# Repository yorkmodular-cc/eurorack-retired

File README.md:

# eurorack-retired

This repo contains schematics, panel files and suchlike for my 'retired' and/or discontinued Eurorack modules. 

They are placed here in the hope that they may be useful to some people - in a lot of the cases I've either refined the design or shelved it altogether. No warranty is given or implied - all of the designs are known to work but I accept no responsibility if you screw something up.

This info is free and unencumbered and released into the public domain.

In jurisdictions that recognize copyright laws, the author or authors
of this software dedicate any and all copyright interest in the
software to the public domain. We make this dedication for the benefit
of the public at large and to the detriment of our heirs and
successors. We intend this dedication to be an overt act of
relinquishment in perpetuity of all present and future rights to this
information e under copyright law.

THESE DESIGNS ARE PROVIDED "AS IS", WITHOUT WARRANTY OF ANY KIND,
EXPRESS OR IMPLIED, INCLUDING BUT NOT LIMITED TO THE WARRANTIES OF
MERCHANTABILITY, FITNESS FOR A PARTICULAR PURPOSE AND NONINFRINGEMENT.
IN NO EVENT SHALL THE AUTHORS BE LIABLE FOR ANY CLAIM, DAMAGES OR
OTHER LIABILITY, WHETHER IN AN ACTION OF CONTRACT, TORT OR OTHERWISE,
ARISING FROM, OUT OF OR IN CONNECTION WITH THE SOFTWARE OR THE USE OR
OTHER DEALINGS IN THE SOFTWARE.

For more information, please refer to <http://unlicense.org/>

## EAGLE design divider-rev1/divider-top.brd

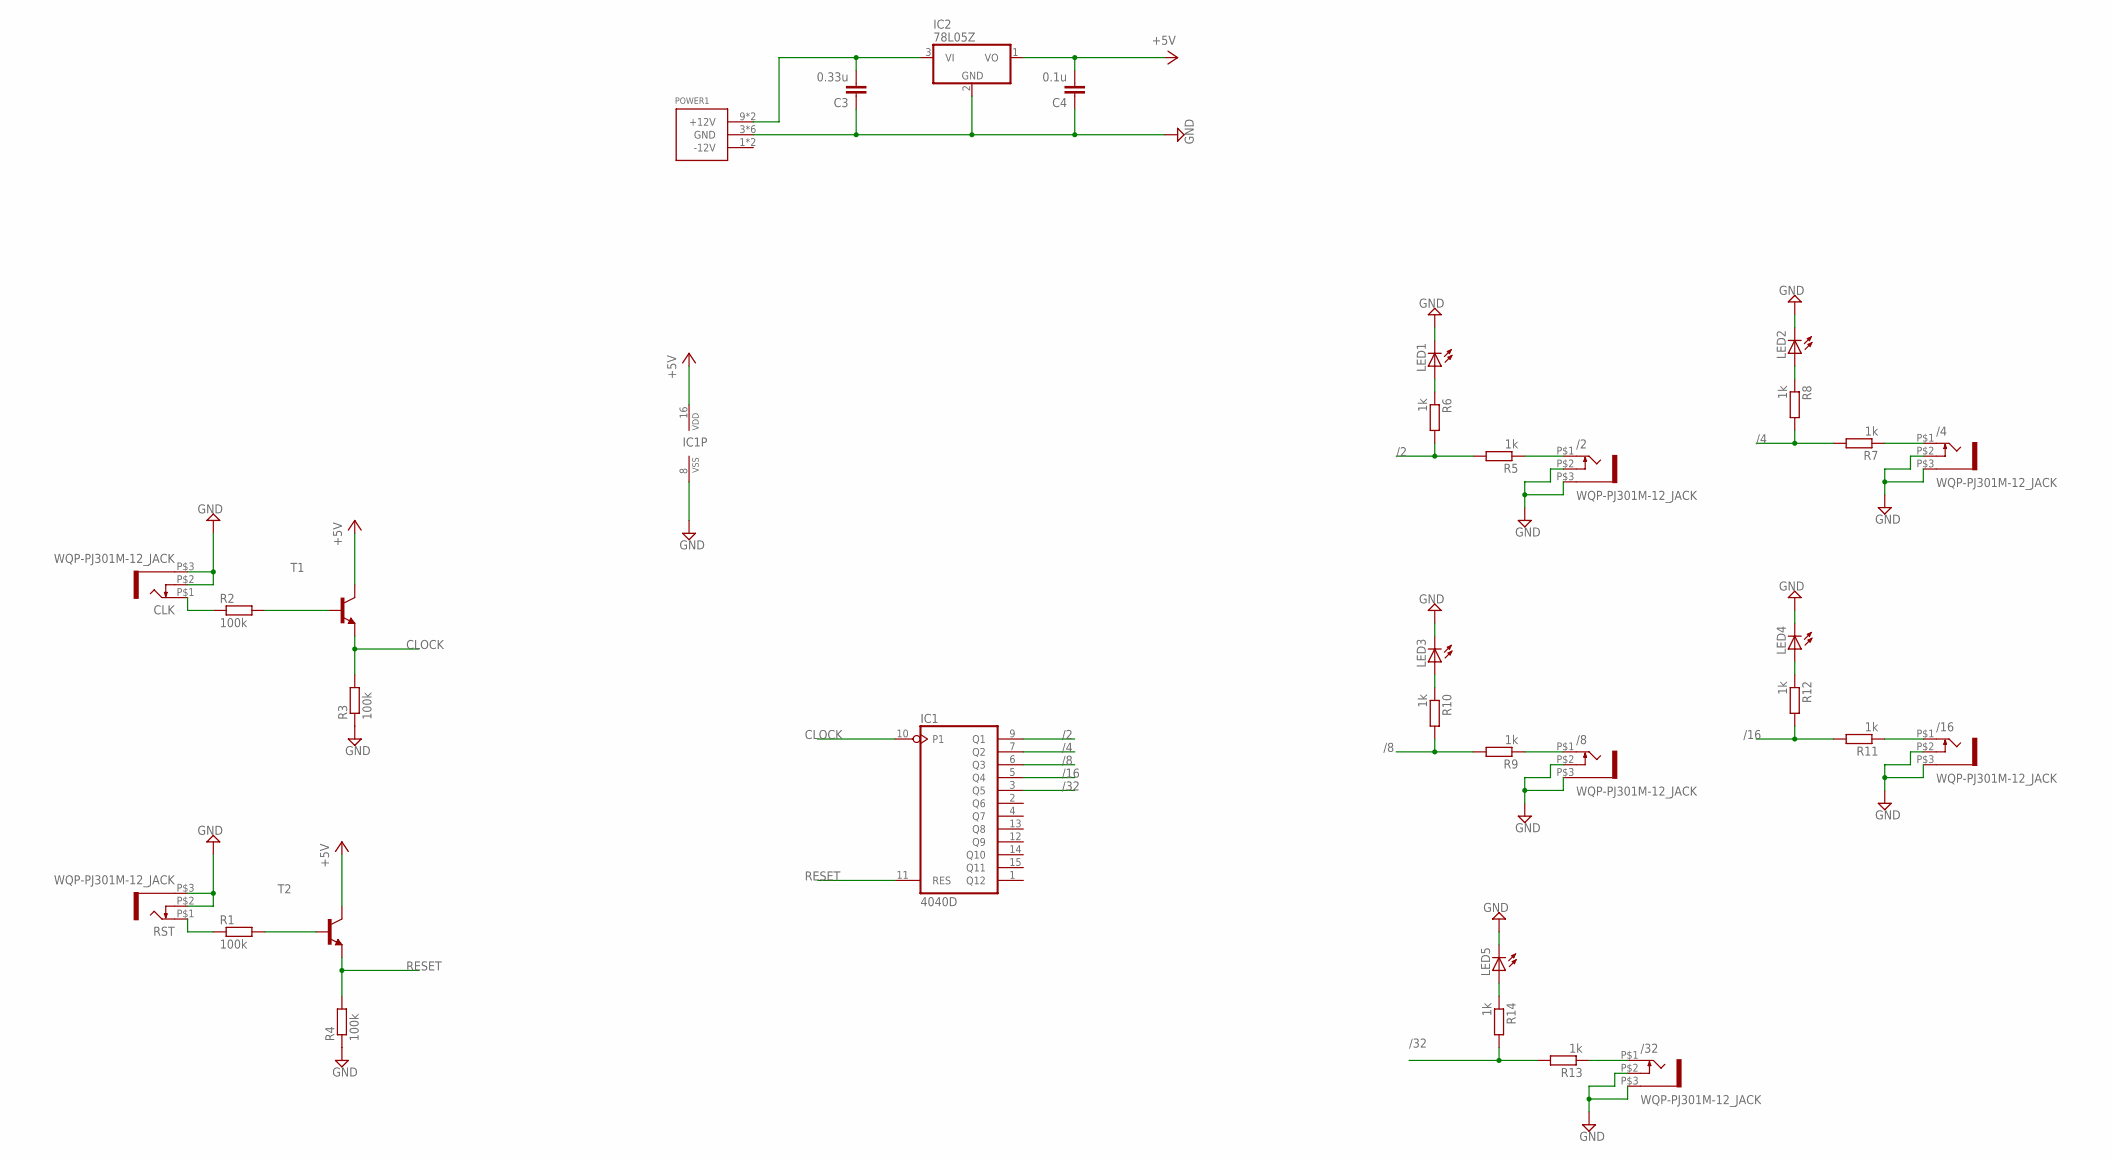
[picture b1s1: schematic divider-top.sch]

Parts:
/2, /4, /8, /16, /32: WQP-PJ301M-12_JACK
C3: 0.33u; C0805
C4: 0.1u; C0805
CLK: WQP-PJ301M-12_JACK
IC1: 4040D; SO16
IC2: 78L05Z; TO92
LED1, LED2, LED3, LED4, LED5: LEDCHIP-LED0805; CHIP-LED0805
POWER1: POWER_SIMPLE10; POWER_10
R1, R2, R3, R4: 100k; R0805
R5, R6, R7, R8, R9, R10, R11, R12, R13, R14: 1k; R0805
RST: WQP-PJ301M-12_JACK
T1, T2: MMBT3904LT1-NPN-SOT23-BEC; SOT23-BEC

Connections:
+5V: C4.2, IC1.16 (VDD), IC2.1 (VO), T1.C, T2.C
/2: IC1.9 (Q1), R5.2, R6.2
/4: IC1.7 (Q2), R7.2, R8.2
/8: IC1.6 (Q3), R9.2, R10.2
/16: IC1.5 (Q4), R11.2, R12.2
/32: IC1.3 (Q5), R13.2, R14.2
CLOCK: IC1.10 (P1), R3.2, T1.E
GND: /2.P$2 (3), /2.P$3 (1), /4.P$2 (3), /4.P$3 (1), /8.P$2 (3), /8.P$3 (1), /16.P$2 (3), /16.P$3 (1), /32.P$2 (3), /32.P$3 (1), C3.1, C4.1, CLK.P$2 (3), CLK.P$3 (1), IC1.8 (VSS), IC2.2 (GND), LED1.C, LED2.C, LED3.C, LED4.C, LED5.C, POWER1.3 (GND), POWER1.4 (GND), POWER1.5 (GND), POWER1.6 (GND), POWER1.7 (GND), POWER1.8 (GND), R3.1, R4.1, RST.P$2 (3), RST.P$3 (1)
unnamed: R1.1, RST.P$1 (2)
unnamed: R1.2, T2.B
unnamed: CLK.P$1 (2), R2.1
unnamed: /2.P$1 (2), R5.1
unnamed: R2.2, T1.B
unnamed: /32.P$1 (2), R13.1
unnamed: LED1.A, R6.1
unnamed: LED5.A, R14.1
unnamed: /4.P$1 (2), R7.1
unnamed: LED2.A, R8.1
unnamed: /8.P$1 (2), R9.1
unnamed: LED3.A, R10.1
unnamed: /16.P$1 (2), R11.1
unnamed: LED4.A, R12.1
unnamed: C3.2, IC2.3 (VI), POWER1.9 (+12V), POWER1.10 (+12V)
RESET: IC1.11 (RES), R4.2, T2.E

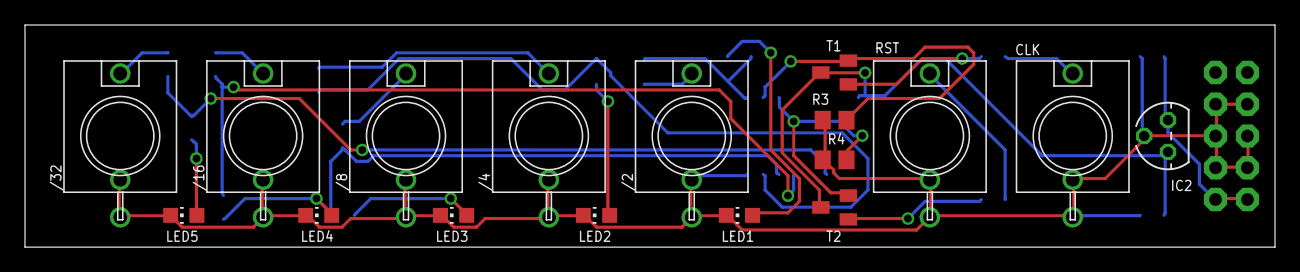
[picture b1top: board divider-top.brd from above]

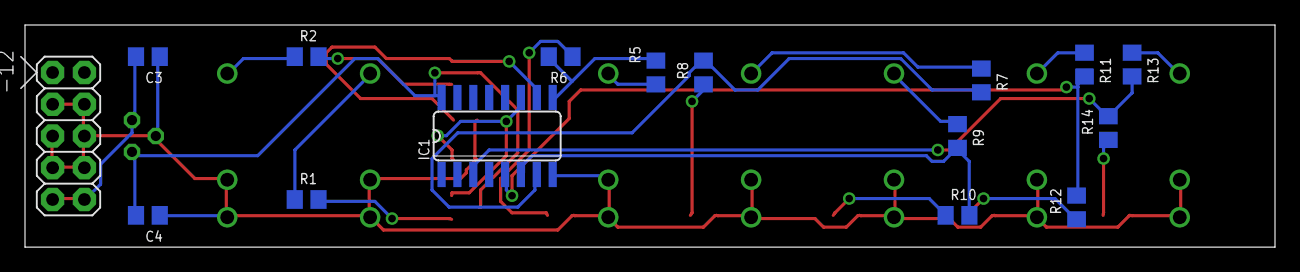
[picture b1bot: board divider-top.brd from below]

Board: 2 copper layers, 100.0 x 17.8 mm, 33 parts (16 on the bottom side), 24 nets.

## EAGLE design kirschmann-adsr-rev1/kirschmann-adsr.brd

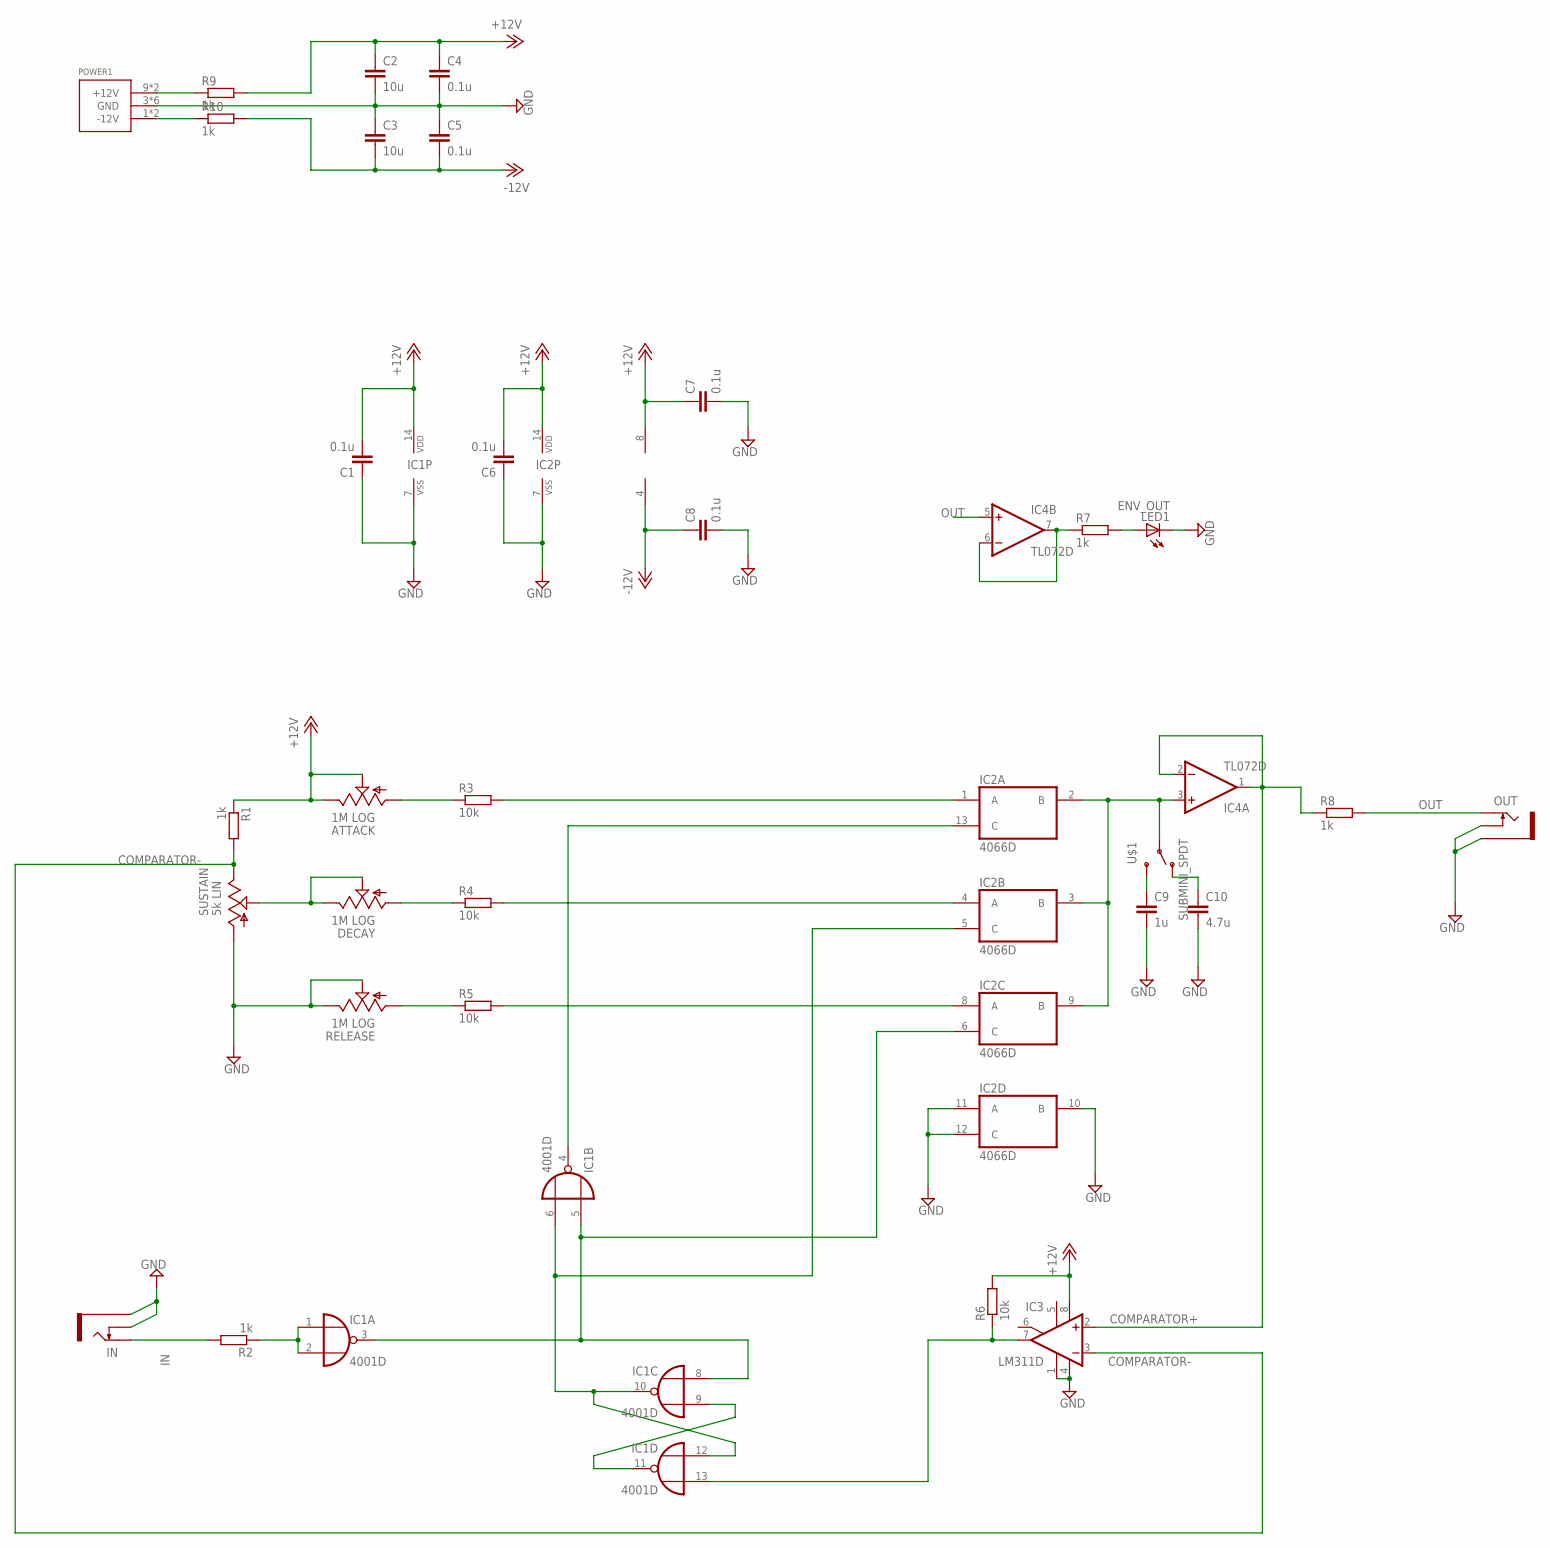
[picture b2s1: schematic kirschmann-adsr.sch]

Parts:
ATTACK: 1M LOG; 9MM_SNAP-IN_POT
C1, C4, C5, C6, C7, C8: 0.1u; C0805
C2, C3: 10u; C0805
C9: 1u; C0805
C10: 4.7u; C0805
DECAY: 1M LOG; 9MM_SNAP-IN_POT
IC1: 4001D; SO14
IC2: 4066D; SO14
IC3: LM311D; SO08
IC4: TL072D; SO08
IN: THONKICONNNEW; WQP-PJ301M-12_JACK
LED1: ENV_OUT; LED3MM
OUT: THONKICONNNEW; WQP-PJ301M-12_JACK
POWER1: POWER_SIMPLE10; POWER_10
R1, R2, R7, R8, R9, R10: 1k; R0805
R3, R4, R5, R6: 10k; R0805
RELEASE: 1M LOG; 9MM_SNAP-IN_POT
SUSTAIN: 5k LIN; 9MM_SNAP-IN_POT
U$1: SUBMINI_SPDT; SUBMINI_TOGGLE

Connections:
+12V: ATTACK.2 (S), ATTACK.3 (E), C1.2, C2.1, C4.1, C6.2, C7.1, IC1.14 (VDD), IC2.14 (VDD), IC3.8 (V+), IC4.8 (V+), R1.1, R6.2, R9.2
-12V: C3.2, C5.2, C8.1, IC4.4 (V-), R10.2
COMPARATOR+: IC3.2 (+IN), IC4.1 (OUT), IC4.2 (-IN), R8.1
COMPARATOR-: IC3.3 (-IN), R1.2, SUSTAIN.3 (E)
GND: C1.1, C2.2, C3.1, C4.2, C5.1, C6.1, C7.2, C8.2, C9.2, C10.2, IC1.7 (VSS), IC2.7 (VSS), IC2.10 (B), IC2.11 (A), IC2.12 (C), IC3.1 (GND), IC3.4 (V-), IN.P$2_SWITCH (SWITCH), IN.P$3_SLEEVE (SLEEVE), LED1.K (C), OUT.P$2_SWITCH (SWITCH), OUT.P$3_SLEEVE (SLEEVE), POWER1.3 (GND), POWER1.4 (GND), POWER1.5 (GND), POWER1.6 (GND), POWER1.7 (GND), POWER1.8 (GND), RELEASE.2 (S), RELEASE.3 (E), SUSTAIN.1 (A)
IN: IN.P$1_TIP (TIP), R2.2
unnamed: IC1.6 (I1), IC1.10 (O), IC1.12 (I0), IC2.5 (C)
unnamed: IC1.9 (I1), IC1.11 (O)
unnamed: IC2.8 (A), R5.2
unnamed: C9.1, U$1.3 (S)
unnamed: IC1.13 (I1), IC3.7 (OUT), R6.1
unnamed: DECAY.1 (A), R4.1
unnamed: R5.1, RELEASE.1 (A)
unnamed: IC1.3 (O), IC1.5 (I0), IC1.8 (I0), IC2.6 (C)
unnamed: IC1.4 (O), IC2.13 (C)
unnamed: IC2.2 (B), IC2.3 (B), IC2.9 (B), IC4.3 (+IN), U$1.COM (COMMON)
unnamed: C10.1, U$1.1 (O)
unnamed: IC1.1 (I0), IC1.2 (I1), R2.1
unnamed: IC2.4 (A), R4.2
unnamed: IC2.1 (A), R3.2
unnamed: IC4.6 (-IN), IC4.7 (OUT), R7.1
unnamed: LED1.A, R7.2
unnamed: DECAY.2 (S), DECAY.3 (E), SUSTAIN.2 (S)
unnamed: POWER1.9 (+12V), POWER1.10 (+12V), R9.1
unnamed: ATTACK.1 (A), R3.1
unnamed: POWER1.1 (-12V), POWER1.2 (-12V), R10.1
OUT: IC4.5 (+IN), OUT.P$1_TIP (TIP), R8.2

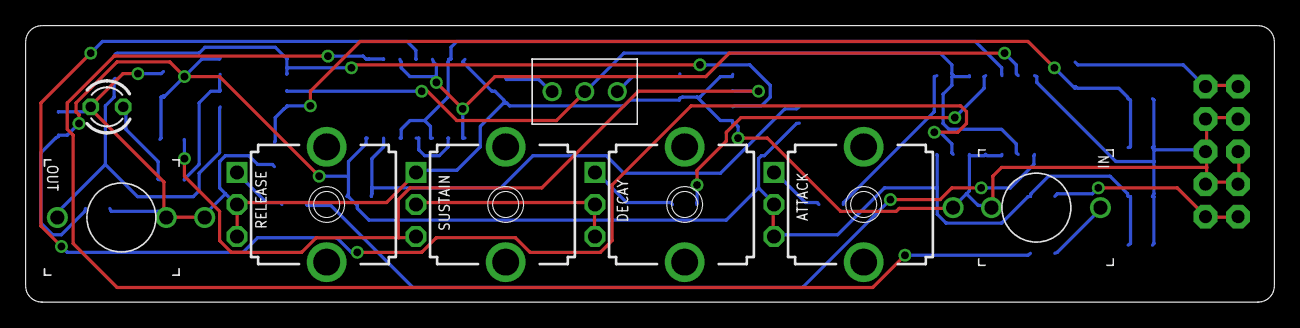
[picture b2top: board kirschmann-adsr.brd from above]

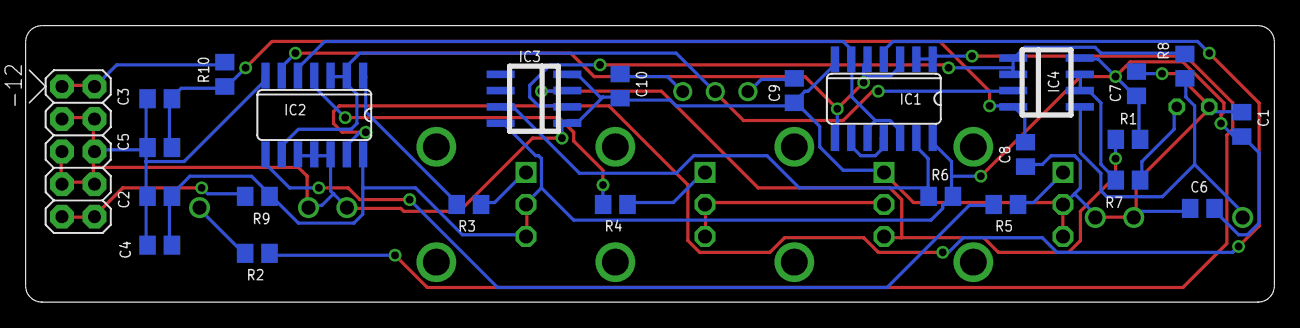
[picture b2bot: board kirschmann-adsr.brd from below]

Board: 2 copper layers, 97.5 x 21.6 mm, 33 parts (25 on the bottom side), 27 nets.

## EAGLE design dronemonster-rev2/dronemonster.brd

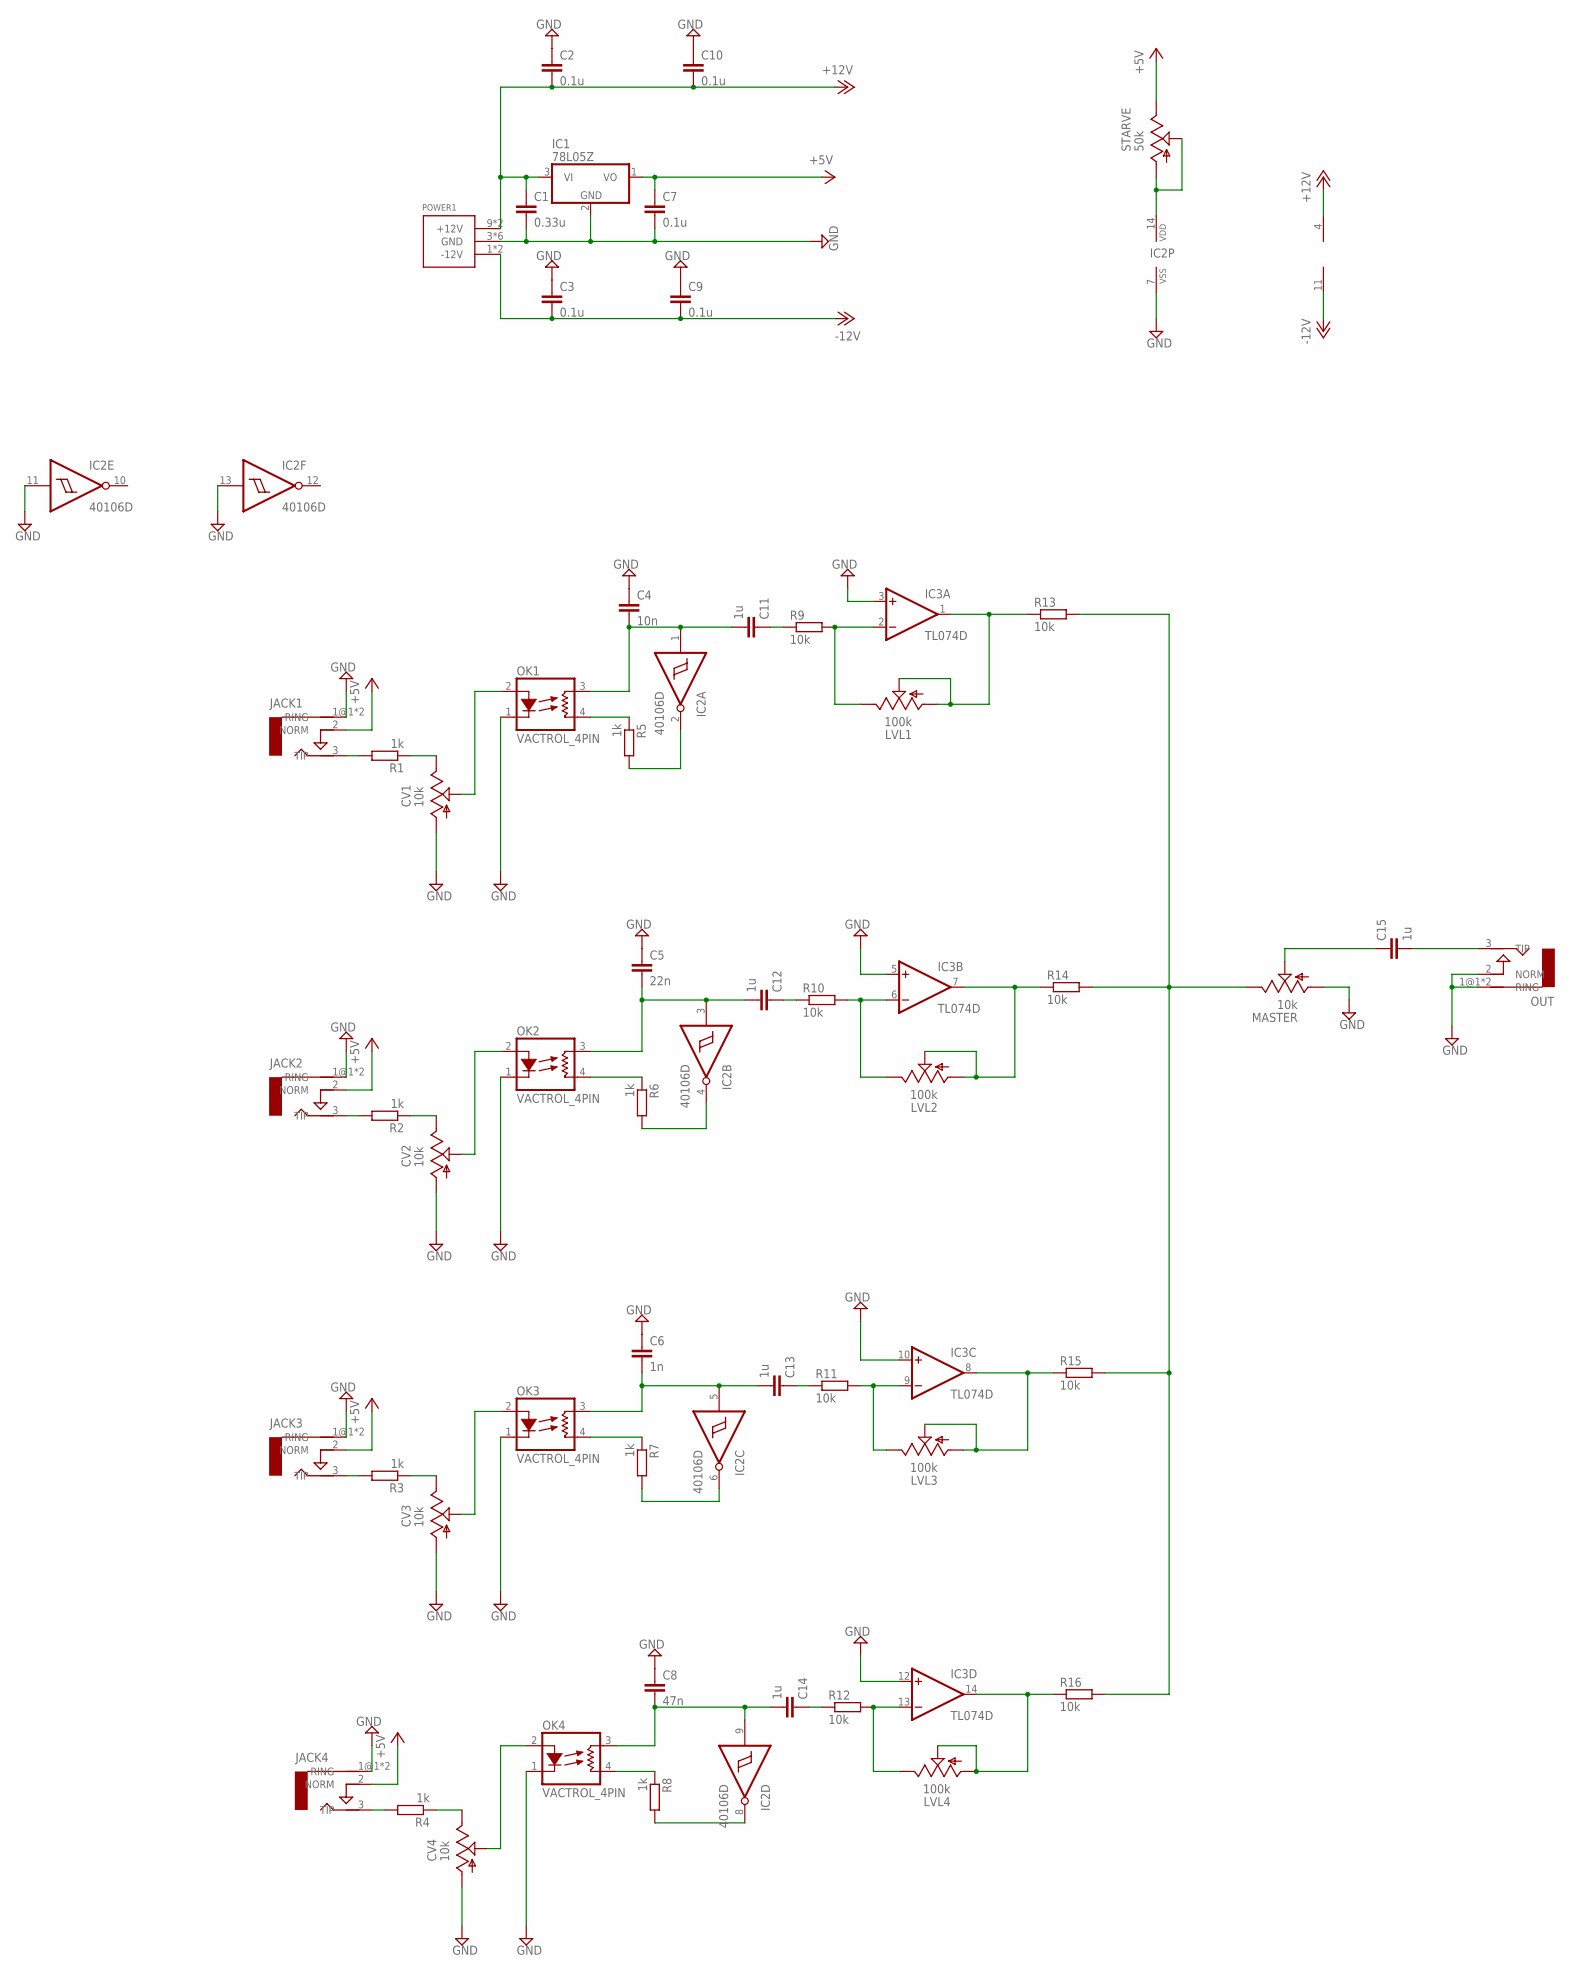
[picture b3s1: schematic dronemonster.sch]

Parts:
C1: 0.33u; C0805
C2, C3, C7, C9, C10: 0.1u; C0805
C4: 10n; C0805
C5: 22n; C0805
C6: 1n; C0805
C8: 47n; C0805
C11, C12, C13, C14, C15: 1u; C0805
CV1, CV2, CV3, CV4: 10k; 9MM_SNAP-IN_POT
IC1: 78L05Z; TO92
IC2: 40106D; SO14
IC3: TL074D; SO14
JACK1: IN1; ERTHENVAR-JACK
JACK2: IN2; ERTHENVAR-JACK
JACK3: IN3; ERTHENVAR-JACK
JACK4: IN4; ERTHENVAR-JACK
LVL1, LVL2, LVL3, LVL4: 100k; 9MM_SNAP-IN_POT
MASTER: 10k; 9MM_SNAP-IN_POT
OK1, OK2, OK3, OK4: VACTROL_4PIN; VACTROL_4PIN_VTL5C
OUT: OUT; ERTHENVAR-JACK
POWER1: POWER_SIMPLE10; POWER_10
R1, R2, R3, R4, R5, R6, R7, R8: 1k; R0805
R9, R10, R11, R12, R13, R14, R15, R16: 10k; R0805
STARVE: 50k; 9MM_SNAP-IN_POT

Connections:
+5V: C7.1, IC1.1 (VO), JACK1.2 (NORM), JACK2.2 (NORM), JACK3.2 (NORM), JACK4.2 (NORM), STARVE.3 (E)
+12V: C1.1, C2.2, C10.2, IC1.3 (VI), IC3.4 (V+), POWER1.9 (+12V), POWER1.10 (+12V)
-12V: C3.2, C9.2, IC3.11 (V-), POWER1.1 (-12V), POWER1.2 (-12V)
GND: C1.2, C2.1, C3.1, C4.1, C5.1, C6.1, C7.2, C8.1, C9.1, C10.1, CV1.1 (A), CV2.1 (A), CV3.1 (A), CV4.1 (A), IC1.2 (GND), IC2.7 (VSS), IC2.11 (I), IC2.13 (I), IC3.3 (+IN), IC3.5 (+IN), IC3.10 (+IN), IC3.12 (+IN), JACK1.1@1 (RING), JACK1.1@2 (RING), JACK2.1@1 (RING), JACK2.1@2 (RING), JACK3.1@1 (RING), JACK3.1@2 (RING), JACK4.1@1 (RING), JACK4.1@2 (RING), MASTER.1 (A), OK1.1 (LED-), OK2.1 (LED-), OK3.1 (LED-), OK4.1 (LED-), OUT.1@1 (RING), OUT.1@2 (RING), OUT.2 (NORM), POWER1.3 (GND), POWER1.4 (GND), POWER1.5 (GND), POWER1.6 (GND), POWER1.7 (GND), POWER1.8 (GND)
unnamed: C14.1, R12.1
unnamed: IC2.14 (VDD), STARVE.1 (A), STARVE.2 (S)
unnamed: JACK1.3 (TIP), R1.2
unnamed: CV1.2 (S), OK1.2 (LED+)
unnamed: C15.1, MASTER.2 (S)
unnamed: CV1.3 (E), R1.1
unnamed: C13.1, R11.1
unnamed: C12.1, R10.1
unnamed: C11.1, R9.1
unnamed: CV2.3 (E), R2.1
unnamed: IC3.13 (-IN), LVL4.3 (E), R12.2
unnamed: JACK2.3 (TIP), R2.2
unnamed: IC3.9 (-IN), LVL3.3 (E), R11.2
unnamed: CV2.2 (S), OK2.2 (LED+)
unnamed: IC3.6 (-IN), LVL2.3 (E), R10.2
unnamed: CV3.3 (E), R3.1
unnamed: IC3.2 (-IN), LVL1.3 (E), R9.2
unnamed: JACK3.3 (TIP), R3.2
unnamed: IC3.1 (OUT), LVL1.1 (A), LVL1.2 (S), R13.1
unnamed: CV3.2 (S), OK3.2 (LED+)
unnamed: MASTER.3 (E), R13.2, R14.2, R15.2, R16.2
unnamed: CV4.3 (E), R4.1
unnamed: C15.2, OUT.3 (TIP)
unnamed: JACK4.3 (TIP), R4.2
unnamed: CV4.2 (S), OK4.2 (LED+)
unnamed: IC3.14 (OUT), LVL4.1 (A), LVL4.2 (S), R16.1
unnamed: OK4.4 (RES2), R8.1
unnamed: IC2.8 (O), R8.2
unnamed: C8.2, C14.2, IC2.9 (I), OK4.3 (RES1)
unnamed: OK3.4 (RES2), R7.1
unnamed: IC2.6 (O), R7.2
unnamed: C6.2, C13.2, IC2.5 (I), OK3.3 (RES1)
unnamed: OK2.4 (RES2), R6.1
unnamed: IC2.4 (O), R6.2
unnamed: C5.2, C12.2, IC2.3 (I), OK2.3 (RES1)
unnamed: OK1.4 (RES2), R5.1
unnamed: IC2.2 (O), R5.2
unnamed: C4.2, C11.2, IC2.1 (I), OK1.3 (RES1)
unnamed: IC3.8 (OUT), LVL3.1 (A), LVL3.2 (S), R15.1
unnamed: IC3.7 (OUT), LVL2.1 (A), LVL2.2 (S), R14.1

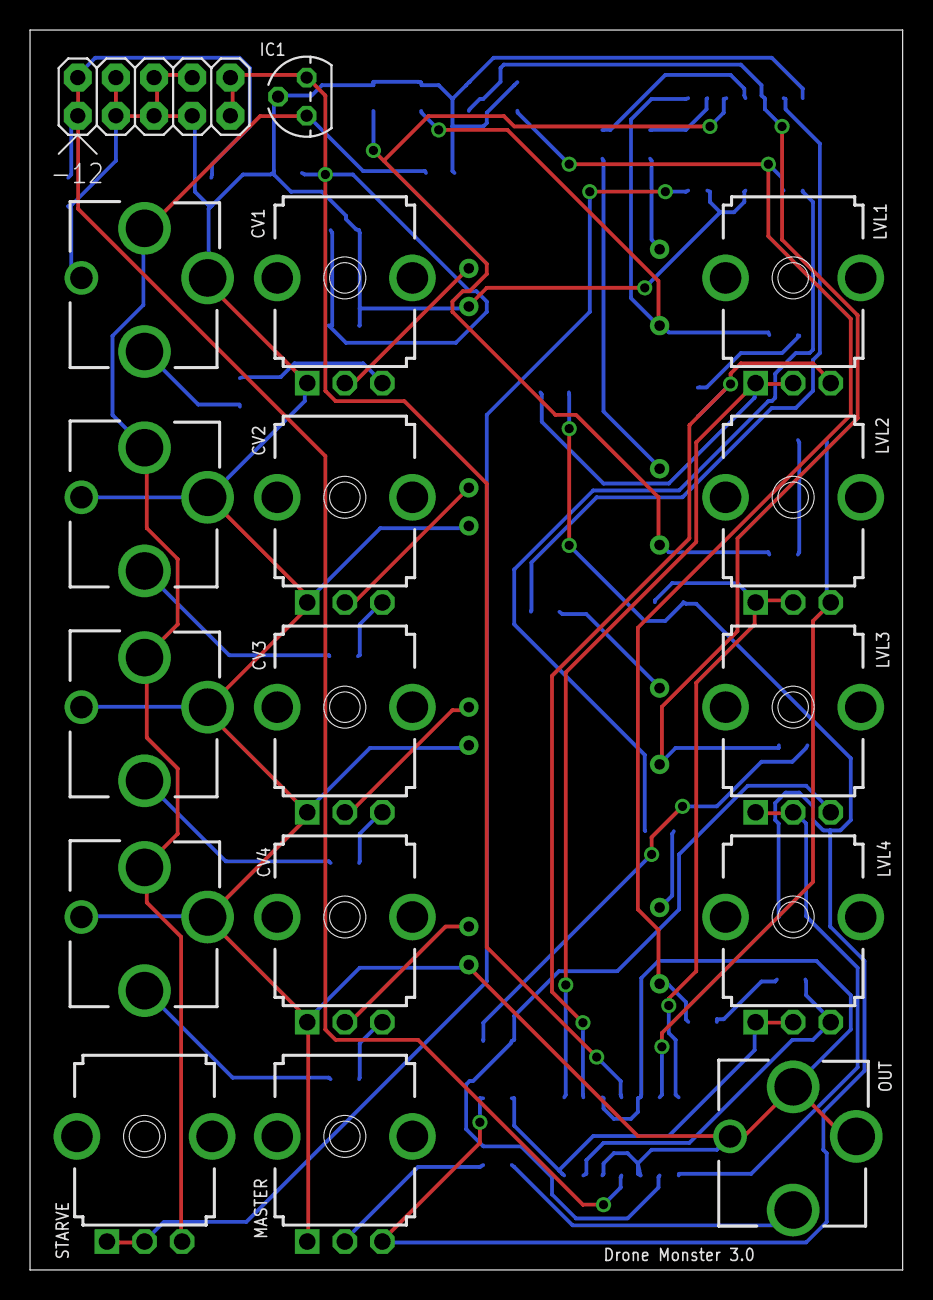
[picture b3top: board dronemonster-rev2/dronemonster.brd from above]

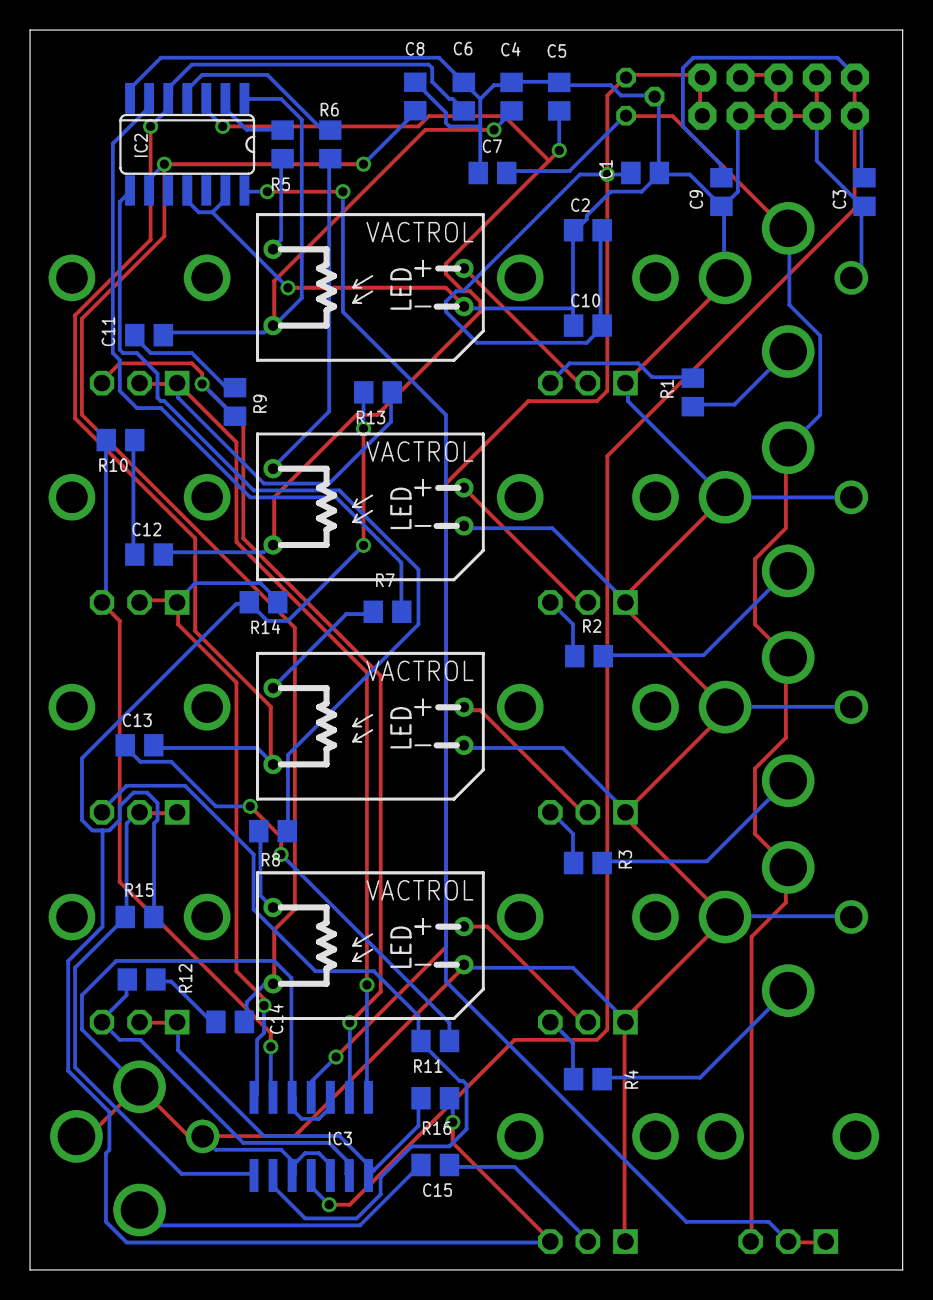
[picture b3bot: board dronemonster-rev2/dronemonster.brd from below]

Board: 2 copper layers, 58.1 x 82.5 mm, 54 parts (37 on the bottom side), 44 nets.

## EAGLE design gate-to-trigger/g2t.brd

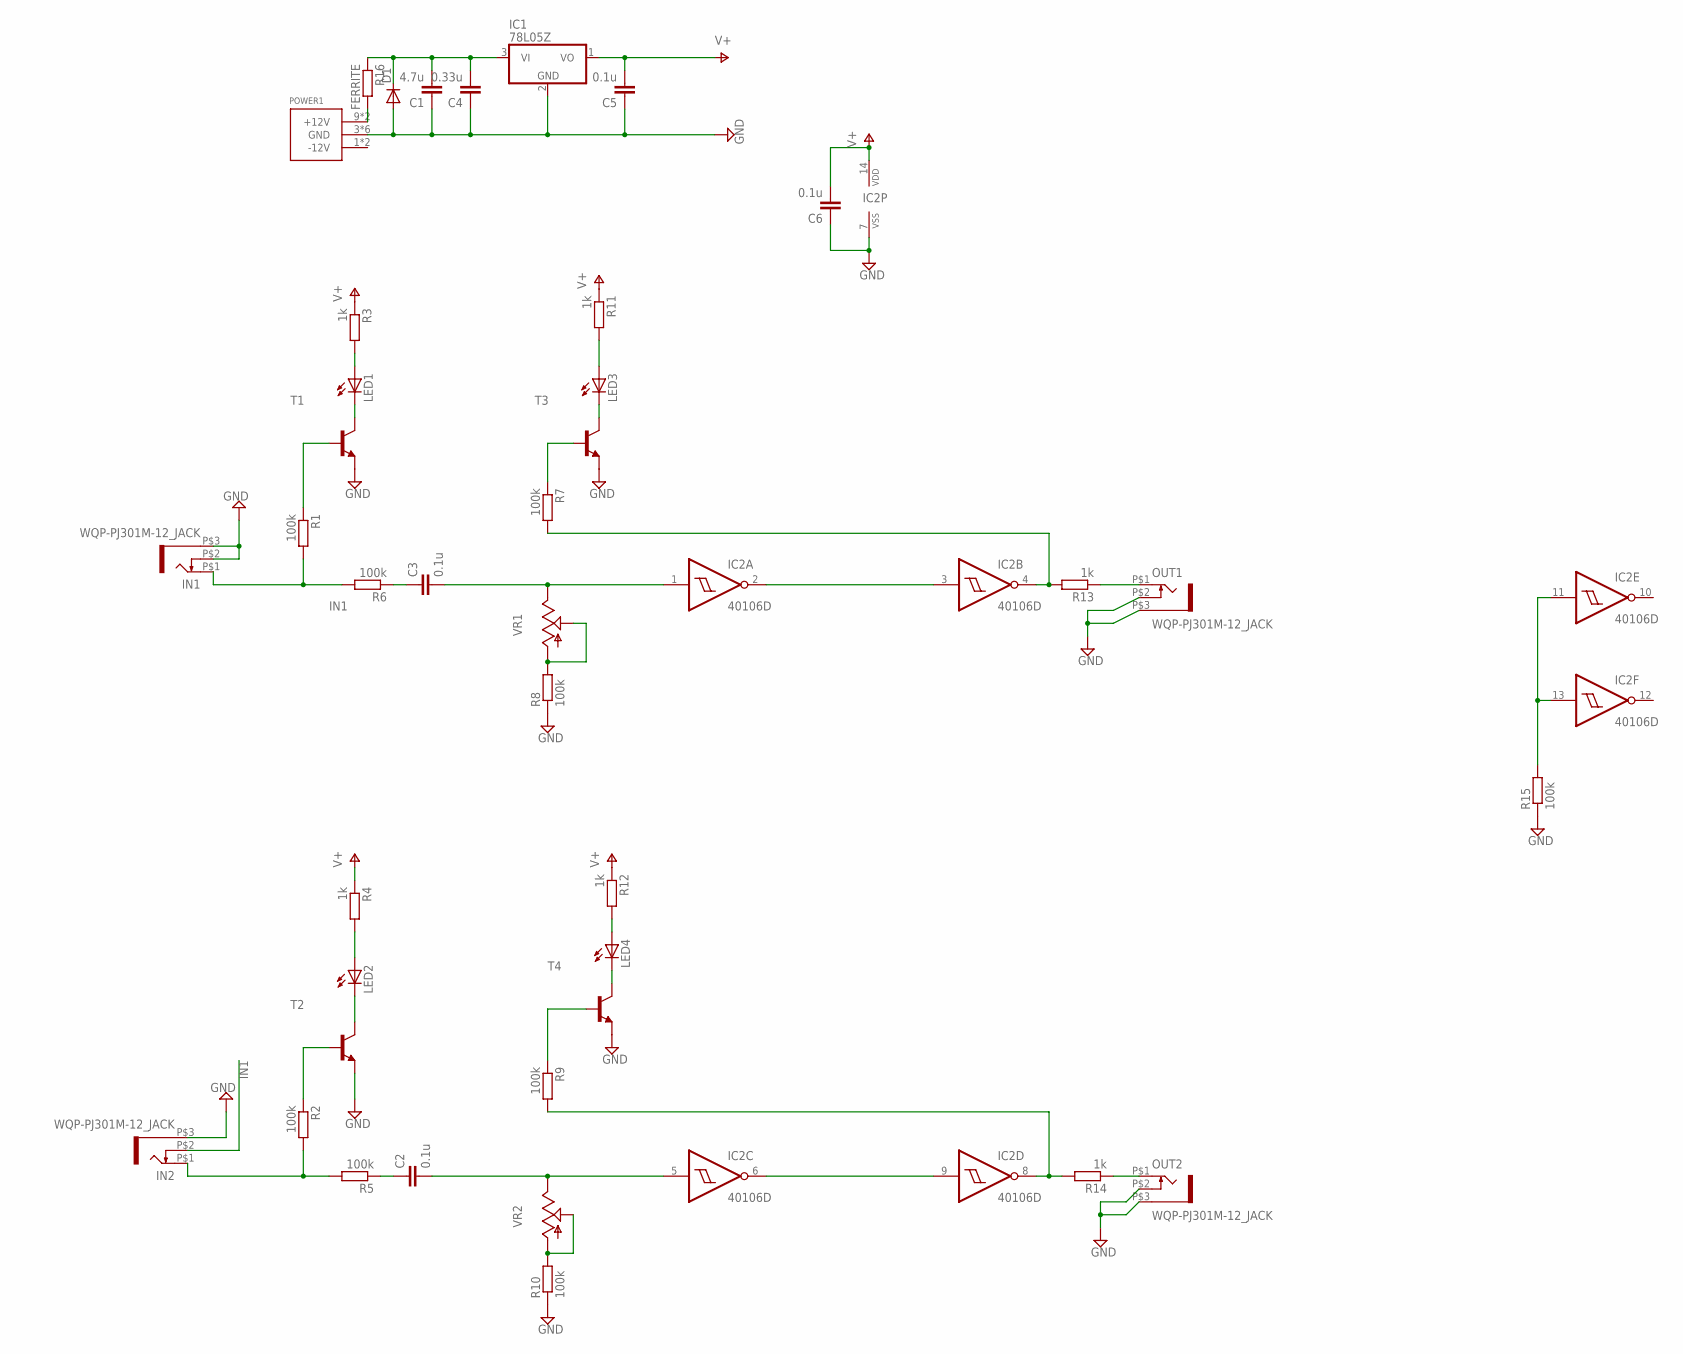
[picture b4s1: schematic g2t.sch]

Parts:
C1: 4.7u; C0805
C2, C3, C5, C6: 0.1u; C0805
C4: 0.33u; C0805
D1: DIODE-SOD323-W; SOD323-W
IC1: 78L05Z; TO92
IC2: 40106D; SO14
IN1, IN2: WQP-PJ301M-12_JACK
LED1, LED2, LED3, LED4: LEDCHIP-LED0805; CHIP-LED0805
OUT1, OUT2: WQP-PJ301M-12_JACK
POWER1: POWER_SIMPLE10; POWER_10
R1, R2, R5, R6, R7, R8, R9, R10, R15: 100k; R0805
R3, R4, R11, R12, R13, R14: 1k; R0805
R16: FERRITE; R0805
T1, T2, T3, T4: MMBT3904LT1-NPN-SOT23-BEC; SOT23-BEC
VR1, VR2: 9MM_SNAP-IN_POT_; 9MM_SNAP-IN_POT

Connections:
GND: C1.1, C4.1, C5.1, C6.1, D1.A, IC1.2 (GND), IC2.7 (VSS), IN1.P$2 (3), IN1.P$3 (1), IN2.P$3 (1), OUT1.P$2 (3), OUT1.P$3 (1), OUT2.P$2 (3), OUT2.P$3 (1), POWER1.3 (GND), POWER1.4 (GND), POWER1.5 (GND), POWER1.6 (GND), POWER1.7 (GND), POWER1.8 (GND), R8.1, R10.1, R15.1, T1.E, T2.E, T3.E, T4.E
IN1: IN1.P$1 (2), IN2.P$2 (3), R1.2, R6.2
IN2: IN2.P$1 (2), R2.2, R5.2
unnamed: IC2.2 (O), IC2.3 (I)
unnamed: IC2.6 (O), IC2.9 (I)
unnamed: IC2.11 (I), IC2.13 (I), R15.2
unnamed: C2.2, IC2.5 (I), VR2.3 (E)
unnamed: C3.2, IC2.1 (I), VR1.3 (E)
unnamed: R8.2, VR1.1 (A), VR1.2 (S)
unnamed: R10.2, VR2.1 (A), VR2.2 (S)
unnamed: R1.1, T1.B
unnamed: POWER1.9 (+12V), POWER1.10 (+12V), R16.2
unnamed: IC2.8 (O), R9.2, R14.2
unnamed: OUT2.P$1 (2), R14.1
unnamed: IC2.4 (O), R7.2, R13.2
unnamed: R7.1, T3.B
unnamed: C2.1, R5.1
unnamed: C1.2, C4.2, D1.C, IC1.3 (VI), R16.1
unnamed: C3.1, R6.1
unnamed: R9.1, T4.B
unnamed: LED3.C, T3.C
unnamed: LED3.A, R11.2
unnamed: LED4.C, T4.C
unnamed: LED4.A, R12.2
unnamed: LED1.C, T1.C
unnamed: LED1.A, R3.2
unnamed: R2.1, T2.B
unnamed: LED2.C, T2.C
unnamed: LED2.A, R4.2
OUT1: OUT1.P$1 (2), R13.1
V+: C5.2, C6.2, IC1.1 (VO), IC2.14 (VDD), R3.1, R4.1, R11.1, R12.1

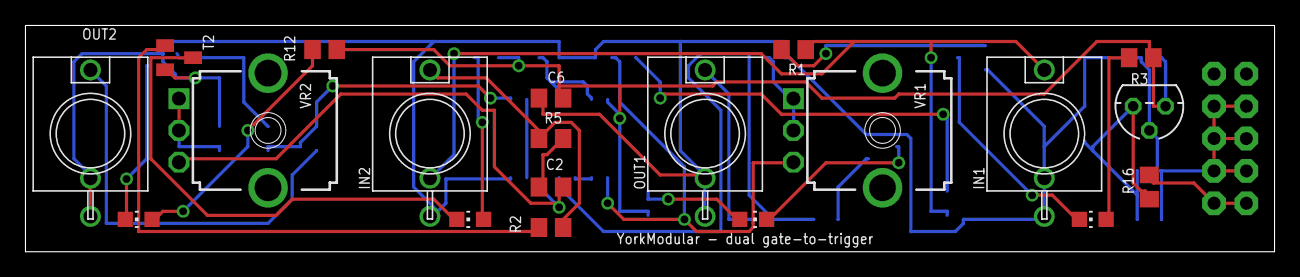
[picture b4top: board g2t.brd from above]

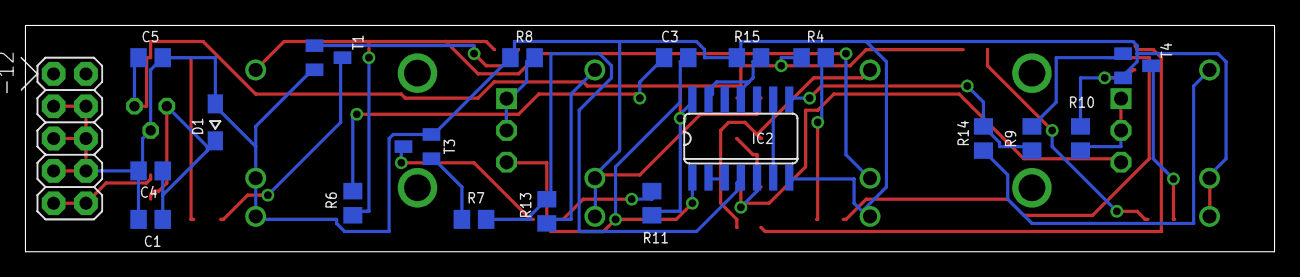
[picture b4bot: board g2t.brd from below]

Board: 2 copper layers, 98.1 x 17.8 mm, 40 parts (20 on the bottom side), 31 nets.
